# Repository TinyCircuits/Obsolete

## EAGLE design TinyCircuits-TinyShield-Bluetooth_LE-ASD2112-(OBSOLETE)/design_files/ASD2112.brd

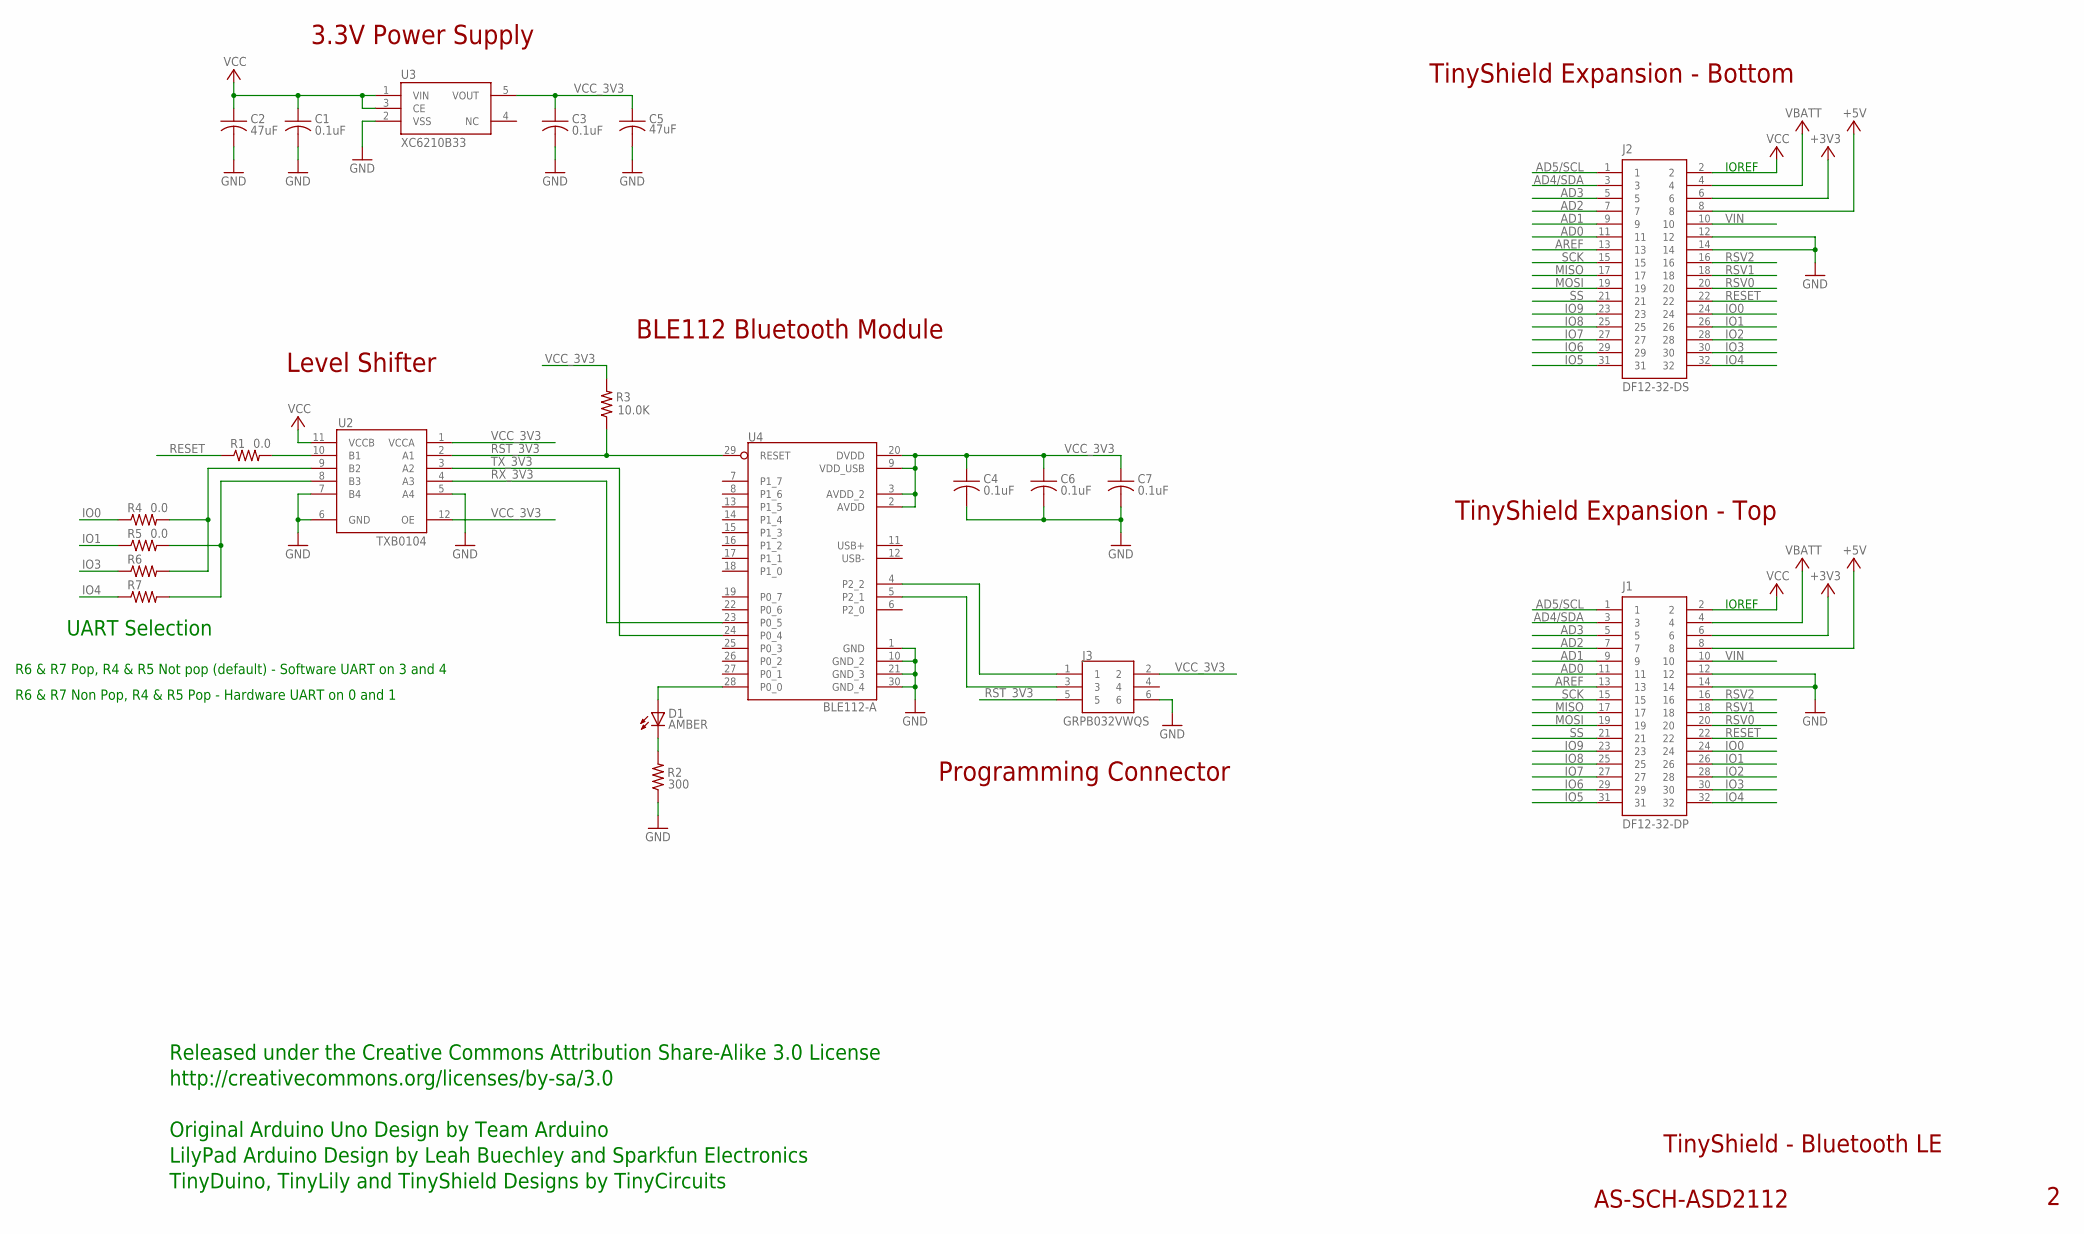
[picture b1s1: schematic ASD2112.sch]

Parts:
C1, C3, C4, C6, C7: 0.1uF; C0402; PARTNO AS-ITM-00008
C2: 47uF; C1206; PARTNUM AS-ITM-00049
C5: 47uF; C1206
D1: AMBER; LNJ_LED
J1: DF12-32-DP; PARTNO AS-ITM-00015
J2: DF12-32-DS; PARTNO AS-ITM-00012
J3: GRPB032VWQS; 2X3_.05"_SMT_HEADER
R1: 0.0; 0402
R2: 300; 0402; PARTNO AS-ITM-00016
R3: 10.0K; 0402
R4, R5: 0.0; 0402; PARTNO AS-ITM-00076
R6, R7: 0.0; 0402_SHORT
U2: TXB0104; UQFN-12
U3: XC6210B33; SOT-25
U4: BLE112-A; BLUEGIGA_BLE_MODULE

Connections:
+3V3: J1.6, J2.6
+5V: J1.8, J2.8
AD0: J1.11, J2.11
AD1: J1.9, J2.9
AD2: J1.7, J2.7
AD3: J1.5, J2.5
AD4/SDA: J1.3, J2.3
AD5/SCL: J1.1, J2.1
AREF: J1.13, J2.13
GND: C1.2, C2.2, C3.2, C4.2, C5.2, C6.2, C7.2, J1.12, J1.14, J2.12, J2.14, J3.6, R2.1, U2.5 (A4), U2.6 (GND), U2.7 (B4), U3.2 (VSS), U4.1 (GND), U4.10 (GND_2), U4.21 (GND_3), U4.30 (GND_4)
IO0: J1.24, J2.24, R4.1
IO1: J1.26, J2.26, R5.1
IO2: J1.28, J2.28
IO3: J1.30, J2.30, R6.1
IO4: J1.32, J2.32, R7.1
IO5: J1.31, J2.31
IO6: J1.29, J2.29
IO7: J1.27, J2.27
IO8: J1.25, J2.25
IO9: J1.23, J2.23
MISO: J1.17, J2.17
MOSI: J1.19, J2.19
unnamed: D1.A, U4.28 (P0_0)
unnamed: R4.2, R6.2, U2.9 (B2)
unnamed: R5.2, R7.2, U2.8 (B3)
unnamed: J3.3, U4.5 (P2_1)
unnamed: R1.2, U2.10 (B1)
unnamed: J3.1, U4.4 (P2_2)
unnamed: D1.C, R2.2
RESET: J1.22, J2.22, R1.1
RST_3V3: J3.5, R3.1, U2.2 (A1), U4.29 (RESET)
RSV0: J1.20, J2.20
RSV1: J1.18, J2.18
RSV2: J1.16, J2.16
RX_3V3: U2.4 (A3), U4.23 (P0_5)
SCK: J1.15, J2.15
SS: J1.21, J2.21
TX_3V3: U2.3 (A2), U4.24 (P0_4)
VBATT: J1.4, J2.4
VCC: C1.1, C2.1, J1.2, J2.2, U2.11 (VCCB), U3.1 (VIN), U3.3 (CE)
VCC_3V3: C3.1, C4.1, C5.1, C6.1, C7.1, J3.2, R3.2, U2.1 (VCCA), U2.12 (OE), U3.5 (VOUT), U4.2 (AVDD), U4.3 (AVDD_2), U4.9 (VDD_USB), U4.20 (DVDD)
VIN: J1.10, J2.10

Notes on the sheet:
TinyShield Expansion - Bottom
TinyShield - Bluetooth LE
AS-SCH-ASD2112
TinyShield Expansion - Top
IOREF
Released under the Creative Commons Attribution Share-Alike 3.0 License
http://creativecommons.org/licenses/by-sa/3.0
LilyPad Arduino Design by Leah Buechley and Sparkfun Electronics
TinyDuino, TinyLily and TinyShield Designs by TinyCircuits
Original Arduino Uno Design by Team Arduino
3.3V Power Supply
BLE112 Bluetooth Module
Level Shifter
Programming Connector
UART Selection
R6 & R7 Pop, R4 & R5 Not pop (default) - Software UART on 3 and 4
R6 & R7 Non Pop, R4 & R5 Pop - Hardware UART on 0 and 1

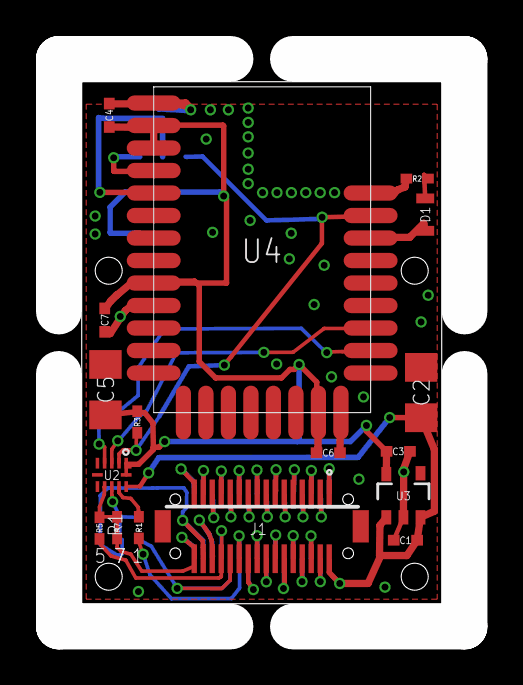
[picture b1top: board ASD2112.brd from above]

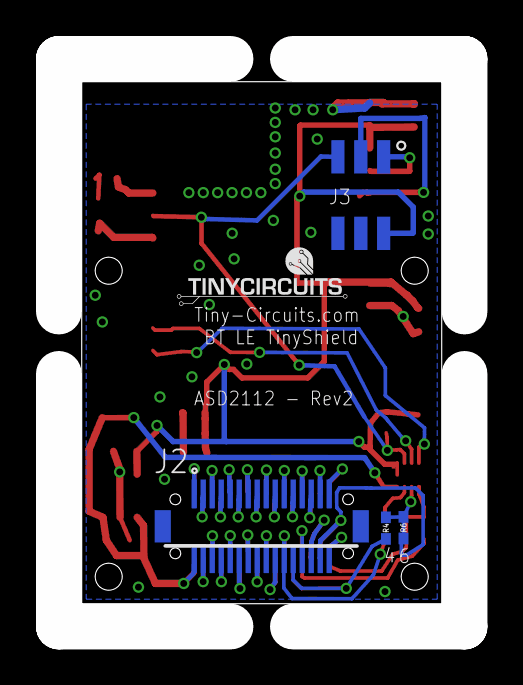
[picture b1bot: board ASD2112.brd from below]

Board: 2 copper layers, 20.0 x 29.0 mm, 22 parts (4 on the bottom side), 42 nets.

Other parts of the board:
U$1: DOCFIELD-TINYCIRCUITS-PCB

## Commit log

2019-06-24 refresh
2019-06-24 updated images
2019-06-24 image fix
2019-06-24 added .zip file
